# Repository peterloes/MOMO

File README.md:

# Multifunctional mainboard to observe and manipulate organisms (MOMO)
[\[paper\]](https://besjournals.onlinelibrary.wiley.com/doi/full/10.1111/1365-2656.13160) 2.3 Nest and feeder monitoring system

Authors: Loës P., Skripsky P., Kempenaers B. (2019) 

Platform for animal observation and manipulation. 

An efficient system to monitor and control animal behaviour in wildlife
as well as in laboratory settings.

- Targeted manipulation of 1000 and more individuals. Selective feeder.
- Supports a broad range of technical applications like e.g. traps, gates, feeders, lights, cameras
-	Compatible with different RFID systems and triggers
-	Low power consumption and specific data collection lead to long lasting collection periods
-	Applicable world-wide due to its compatibility with different types of radio clock receivers 
-	High observation quality through low disturbance to the animals
- Supports data-transfer to external devices, such as personal computers

- Time Synchronization with atomic clock once a day to ensure optimal data quality
- Application Current Control twice a day
- Forecast for Battery-Change implemented
- Energy Bypass so that Date and Time are maintained even when changing battery
- Hyperterminal Output to get real-time data to the computer/laptop
- Low-Power Device:sleep: 220µA@12V with Light_Barrier awake: 12mA@12V

Bird Feeder Application:

https://github.com/peterloes/MOMO/blob/master/Getting_Started_Tutorial/1_poster_overview_3.pdf

Raw data on SD Card:

https://github.com/peterloes/MOMO/blob/master/Getting_Started_Tutorial/6_rawdata_BOX1005.TXT

Configuration data on SD Card:

https://github.com/peterloes/MOMO/blob/master/Software/CONFIG.TXT

Optional components: 

https://github.com/peterloes/Light_Barrier

https://github.com/peterloes/Servo_Engine

https://github.com/peterloes/Linear_Engine

https://github.com/peterloes/Booter_RFID-MS_MOMO_TAMDL

https://github.com/peterloes/Clock_receiver_RFID-MS_MOMO_TAMDL

Manufacture:

https://github.com/peterloes/MOMO/blob/master/Getting_Started_Tutorial/5_Supplier.txt

EXTENSIONS

Application Scales: Outdoor weighing system for animals include RFID-reader

https://github.com/peterloes/Scales

Application Audio: Record and playback soundfiles triggered by (RFID) pit-tag numbers

https://github.com/peterloes/Audio

C is the Greenest Programming Language

To achieve its power and energy-efficiency features, EFM32 products utilize ultralow active and idle power,
fast wakeup and processing times, and most important, the ability to intelligently interact with peripherals
and sensors autonomously without waking up the CPU and consuming more power.

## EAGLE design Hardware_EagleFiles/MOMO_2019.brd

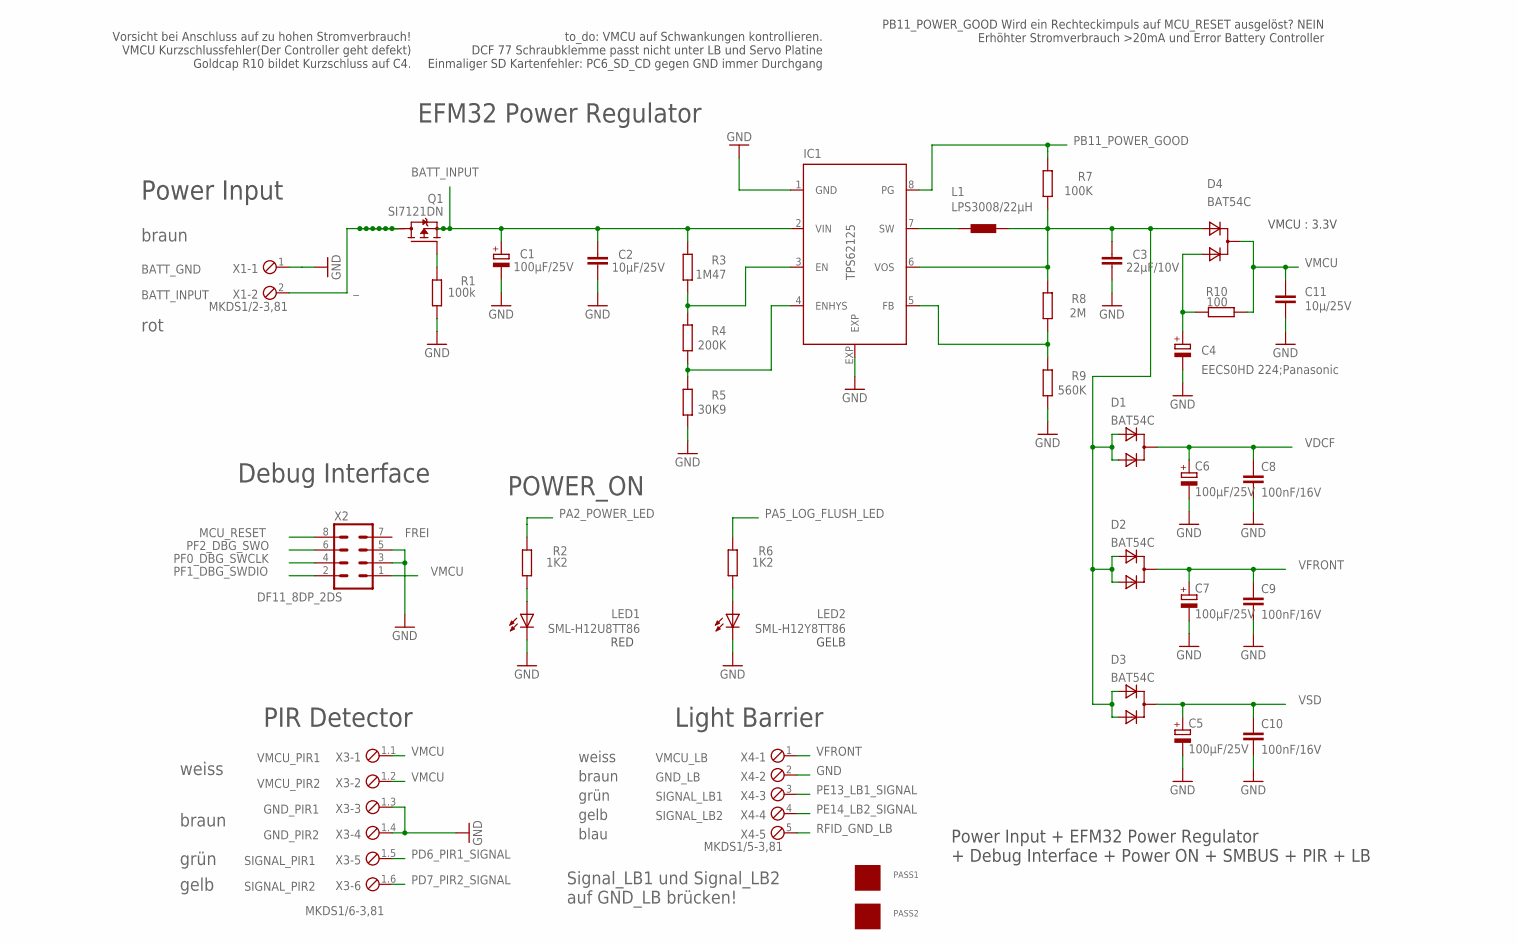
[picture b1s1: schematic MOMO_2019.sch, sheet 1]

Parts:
C1, C5, C6, C7: 100µF/25V; PANASONIC_E
C2: 10µF/25V; C1206
C3: 22µF/10V; C0603
C4: EECS0HD 224;Panasonic; GOLDCAPSPK-V
C8, C9, C10: 100nF/16V; C0805
C11: 10µ/25V; C1206
D1, D2, D3, D4: BAT54C; SOT-23$1
IC1: TPS62125; DSG_PWSO-N8_EXP
L1: LPS3008/22µH; LPS3008
LED1: SML-H12U8TT86; CHIPLED_0805
LED2: SML-H12Y8TT86; CHIPLED_0805
PASS1, PASS2: ROUND_1MM1.5; ROUND2_1.5MM
Q1: SI7121DN; TRANSISTOR-FET_1212-8S
R1: 100k; R0805
R2, R6: 1K2; R0805
R3: 1M47; R0805
R4: 200K; R0805
R5: 30K9; R0805
R7: 100K; R0805
R8: 2M; R0805
R9: 560K; R0805
R10: 100; R0805
X1: MKDS1/2-3,81; 2POL381
X2: DF11_8DP_2DS; DP11_8DP-2DS
X3: MKDS1/6-3,81; 6POL381
X4: MKDS1/5-3,81; 5POL381

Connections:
1: C3.1, D1.2 (A1), D1.3 (A2), D2.2 (A1), D2.3 (A2), D3.2 (A1), D3.3 (A2), D4.2 (A1), IC1.6 (VOS), L1.2, R7.1, R8.2
BATT_INPUT: C1.+, C2.1, IC1.2 (VIN), Q1.1 (S), Q1.2 (S), Q1.3 (S), R3.2; also elsewhere on the board
GND: C1.-, C2.2, C3.2, C4.-, C5.-, C6.-, C7.-, C8.2, C9.2, C10.2, C11.1, IC1.1 (GND), IC1.EXP, LED1.C, LED2.C, R1.1, R5.1, R9.1, X1.1, X2.3, X2.5, X3.1.3, X3.1.4, X4.2; also elsewhere on the board
MCU_RESET: X2.8; also elsewhere on the board
unnamed: LED2.A, R6.2
unnamed: C4.+, D4.3 (A2), R10.2
unnamed: IC1.3 (EN), R3.1, R4.2
unnamed: IC1.4 (ENHYS), R4.1, R5.2
unnamed: IC1.7 (SW), L1.1
unnamed: Q1.4 (G), R1.2
unnamed: LED1.A, R2.2
unnamed: IC1.5 (FB), R8.1, R9.2
PA2_POWER_LED: R2.1; also elsewhere on the board
PA5_LOG_FLUSH_LED: R6.1; also elsewhere on the board
PB11_POWER_GOOD: IC1.8 (PG), R7.2; also elsewhere on the board
PD6_PIR1_SIGNAL: X3.1.5; also elsewhere on the board
PD7_PIR2_SIGNAL: X3.1.6; also elsewhere on the board
PE13_LB1_SIGNAL: X4.3; also elsewhere on the board
PE14_LB2_SIGNAL: X4.4; also elsewhere on the board
PF0_DBG_SWCLK: X2.4; also elsewhere on the board
PF1_DBG_SWDIO: X2.2; also elsewhere on the board
PF2_DBG_SWO: X2.6; also elsewhere on the board
RFID_GND_LB: X4.5; also elsewhere on the board
VDCF: C6.+, C8.1, D1.1 (C); also elsewhere on the board
VFRONT: C7.+, C9.1, D2.1 (C), X4.1
VMCU: C11.2, D4.1 (C), R10.1, X2.1, X3.1.1, X3.1.2; also elsewhere on the board
VSD: C5.+, C10.1, D3.1 (C); also elsewhere on the board
_: Q1.5 (D), Q1.6 (D), Q1.7 (D), Q1.8 (D), Q1.9 (D), Q1.10 (D), Q1.11 (D), X1.2

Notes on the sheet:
BATT_GND
BATT_INPUT
Power Input + EFM32 Power Regulator + Debug Interface + Power ON + SMBUS + PIR + LB
Power Input
EFM32 Power Regulator
Debug Interface
POWER_ON
FREI
SIGNAL_PIR1
VMCU_PIR1
VMCU_PIR2
GND_PIR1
GND_PIR2
SIGNAL_PIR2
VMCU : 3.3V
weiss
braun
grün
gelb
VMCU_LB
GND_LB
SIGNAL_LB1
SIGNAL_LB2
PIR Detector
Light Barrier
RED
GELB
blau
rot
to_do: VMCU auf Schwankungen kontrollieren. DCF 77 Schraubklemme passt nicht unter LB und Servo Platine Einmaliger SD Kartenfehler: PC6_SD_CD gegen GND immer Durchgang
Vorsicht bei Anschluss auf zu hohen Stromverbrauch! VMCU Kurzschlussfehler(Der Controller geht defekt) Goldcap R10 bildet Kurzschluss auf C4.
PB11_POWER_GOOD Wird ein Rechteckimpuls auf MCU_RESET ausgelöst? NEIN Erhöhter Stromverbrauch >20mA und Error Battery Controller
Signal_LB1 und Signal_LB2 auf GND_LB brücken!

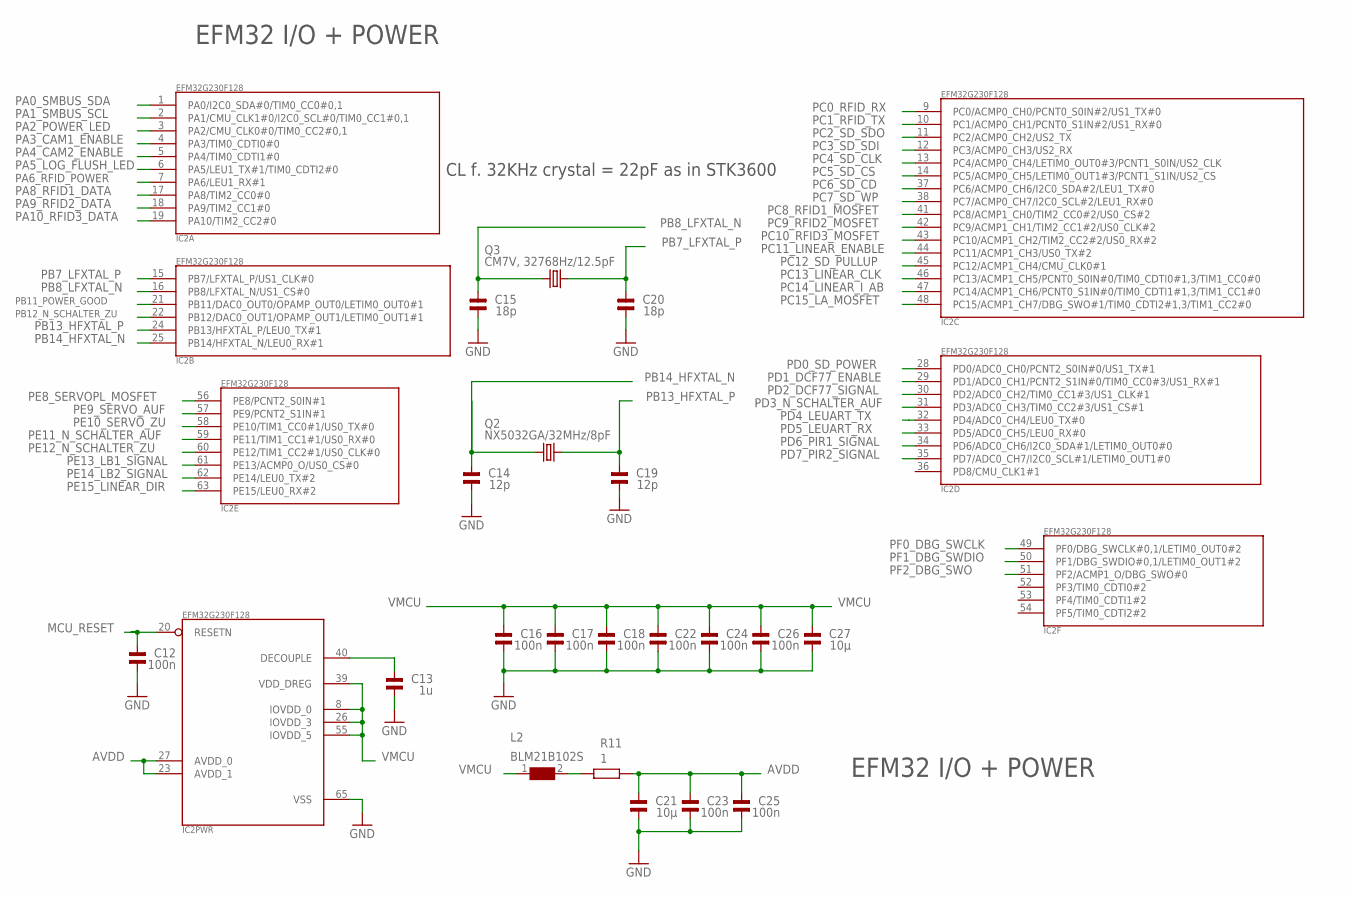
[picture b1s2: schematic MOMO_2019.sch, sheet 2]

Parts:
C12, C16, C17, C18, C22, C23, C24, C25, C26: 100n; 0805
C13: 1u; 0805
C14, C19: 12p; 0805
C15, C20: 18p; 0805
C21, C27: 10µ; 0805
IC2: EFM32G230F128; QFN64
L2: BLM21B102S; 0805
Q2: NX5032GA/32MHz/8pF; CRYSTAL2P5.0X3.2
Q3: CM7V, 32768Hz/12.5pF; CRYSTAL2P3.2X1.5
R11: 1; R0805

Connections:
AVDD: C21.2, C23.2, C25.2, IC2.23 (AVDD_1), IC2.27 (AVDD_0), R11.2
GND: C12.1, C13.1, C14.1, C15.1, C16.1, C17.1, C18.1, C19.1, C20.1, C21.1, C22.1, C23.1, C24.1, C25.1, C26.1, C27.1, IC2.65 (VSS); also elsewhere on the board
MCU_RESET: C12.2, IC2.20 (RESETN); also elsewhere on the board
unnamed: L2.2, R11.1
unnamed: C13.2, IC2.40 (DECOUPLE)
PA0_SMBUS_SDA: IC2.1 (PA0/I2C0_SDA#0/TIM0_CC0#0,1); also elsewhere on the board
PA1_SMBUS_SCL: IC2.2 (PA1/CMU_CLK1#0/I2C0_SCL#0/TIM0_CC1#0,1); also elsewhere on the board
PA2_POWER_LED: IC2.3 (PA2/CMU_CLK0#0/TIM0_CC2#0,1); also elsewhere on the board
PA3_CAM1_ENABLE: IC2.4 (PA3/TIM0_CDTI0#0); also elsewhere on the board
PA4_CAM2_ENABLE: IC2.5 (PA4/TIM0_CDTI1#0); also elsewhere on the board
PA5_LOG_FLUSH_LED: IC2.6 (PA5/LEU1_TX#1/TIM0_CDTI2#0); also elsewhere on the board
PA6_RFID_POWER: IC2.7 (PA6/LEU1_RX#1); also elsewhere on the board
PA8_RFID1_DATA: IC2.17 (PA8/TIM2_CC0#0); also elsewhere on the board
PA9_RFID2_DATA: IC2.18 (PA9/TIM2_CC1#0); also elsewhere on the board
PA10_RFID3_DATA: IC2.19 (PA10/TIM2_CC2#0); also elsewhere on the board
PB7_LFXTAL_P: C20.2, IC2.15 (PB7/LFXTAL_P/US1_CLK#0), Q3.2
PB8_LFXTAL_N: C15.2, IC2.16 (PB8/LFXTAL_N/US1_CS#0), Q3.1
PB11_POWER_GOOD: IC2.21 (PB11/DAC0_OUT0/OPAMP_OUT0/LETIM0_OUT0#1); also elsewhere on the board
PB12_N_SCHALTER_ZU: IC2.22 (PB12/DAC0_OUT1/OPAMP_OUT1/LETIM0_OUT1#1); also elsewhere on the board
PB13_HFXTAL_P: C19.2, IC2.24 (PB13/HFXTAL_P/LEU0_TX#1), Q2.2
PB14_HFXTAL_N: C14.2, IC2.25 (PB14/HFXTAL_N/LEU0_RX#1), Q2.1
PC0_RFID_RX: IC2.9 (PC0/ACMP0_CH0/PCNT0_S0IN#2/US1_TX#0); also elsewhere on the board
PC1_RFID_TX: IC2.10 (PC1/ACMP0_CH1/PCNT0_S1IN#2/US1_RX#0); also elsewhere on the board
PC2_SD_SDO: IC2.11 (PC2/ACMP0_CH2/US2_TX); also elsewhere on the board
PC3_SD_SDI: IC2.12 (PC3/ACMP0_CH3/US2_RX); also elsewhere on the board
PC4_SD_CLK: IC2.13 (PC4/ACMP0_CH4/LETIM0_OUT0#3/PCNT1_S0IN/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); also elsewhere on the board
PC5_SD_CS: IC2.14 (PC5/ACMP0_CH5/LETIM0_OUT1#3/PCNT1_S1IN/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); also elsewhere on the board
PC6_SD_CD: IC2.37 (PC6/ACMP0_CH6/I2C0_SDA#2/LEU1_TX#0); also elsewhere on the board
PC7_SD_WP: IC2.38 (PC7/ACMP0_CH7/I2C0_SCL#2/LEU1_RX#0); also elsewhere on the board
PC8_RFID1_MOSFET: IC2.41 (PC8/ACMP1_CH0/TIM2_CC0#2/US0_CS#2); also elsewhere on the board
PC9_RFID2_MOSFET: IC2.42 (PC9/ACMP1_CH1/TIM2_CC1#2/US0_CLK#2); also elsewhere on the board
PC10_RFID3_MOSFET: IC2.43 (PC10/ACMP1_CH2/TIM2_CC2#2/US0_RX#2); also elsewhere on the board
PC11_LINEAR_ENABLE: IC2.44 (PC11/ACMP1_CH3/US0_TX#2); also elsewhere on the board
PC12_SD_PULLUP: IC2.45 (PC12/ACMP1_CH4/CMU_CLK0#1); also elsewhere on the board
PC13_LINEAR_CLK: IC2.46 (PC13/ACMP1_CH5/PCNT0_S0IN#0/TIM0_CDTI0#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); also elsewhere on the board
PC14_LINEAR_I_AB: IC2.47 (PC14/ACMP1_CH6/PCNT0_S1IN#0/TIM0_CDTI1#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); also elsewhere on the board
PC15_LA_MOSFET: IC2.48 (PC15/ACMP1_CH7/DBG_SWO#1/TIM0_CDTI2#1,3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); also elsewhere on the board
PD0_SD_POWER: IC2.28 (PD0/ADC0_CH0/PCNT2_S0IN#0/US1_TX#1); also elsewhere on the board
PD1_DCF77_ENABLE: IC2.29 (PD1/ADC0_CH1/PCNT2_S1IN#0/TIM0_CC0#3/US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); also elsewhere on the board
PD2_DCF77_SIGNAL: IC2.30 (PD2/ADC0_CH2/TIM0_CC1#3/US1_CLK#1); also elsewhere on the board
PD3_N_SCHALTER_AUF: IC2.31 (PD3/ADC0_CH3/TIM0_CC2#3/US1_CS#1); also elsewhere on the board
PD4_LEUART_TX: IC2.32 (PD4/ADC0_CH4/LEU0_TX#0); also elsewhere on the board
PD5_LEUART_RX: IC2.33 (PD5/ADC0_CH5/LEU0_RX#0); also elsewhere on the board
PD6_PIR1_SIGNAL: IC2.34 (PD6/ADC0_CH6/I2C0_SDA#1/LETIM0_OUT0#0); also elsewhere on the board
PD7_PIR2_SIGNAL: IC2.35 (PD7/ADC0_CH7/I2C0_SCL#1/LETIM0_OUT1#0); also elsewhere on the board
PE8_SERVOPL_MOSFET: IC2.56 (PE8/PCNT2_S0IN#1); also elsewhere on the board
PE9_SERVO_AUF: IC2.57 (PE9/PCNT2_S1IN#1); also elsewhere on the board
PE10_SERVO_ZU: IC2.58 (PE10/TIM1_CC0#1/US0_TX#0); also elsewhere on the board
PE11_N_SCHALTER_AUF: IC2.59 (PE11/TIM1_CC1#1/US0_RX#0); also elsewhere on the board
PE12_N_SCHALTER_ZU: IC2.60 (PE12/TIM1_CC2#1/US0_CLK#0); also elsewhere on the board
PE13_LB1_SIGNAL: IC2.61 (PE13/ACMP0_O/US0_CS#0); also elsewhere on the board
PE14_LB2_SIGNAL: IC2.62 (PE14/LEU0_TX#2); also elsewhere on the board
PE15_LINEAR_DIR: IC2.63 (PE15/LEU0_RX#2); also elsewhere on the board
PF0_DBG_SWCLK: IC2.49 (PF0/DBG_SWCLK#0,1/LETIM0_OUT0#2); also elsewhere on the board
PF1_DBG_SWDIO: IC2.50 (PF1/DBG_SWDIO#0,1/LETIM0_OUT1#2); also elsewhere on the board
PF2_DBG_SWO: IC2.51 (PF2/ACMP1_O/DBG_SWO#0); also elsewhere on the board
VMCU: C16.2, C17.2, C18.2, C22.2, C24.2, C26.2, C27.2, IC2.8 (IOVDD_0), IC2.26 (IOVDD_3), IC2.39 (VDD_DREG), IC2.55 (IOVDD_5), L2.1; also elsewhere on the board

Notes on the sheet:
EFM32 I/O + POWER
CL f. 32KHz crystal = 22pF as in STK3600

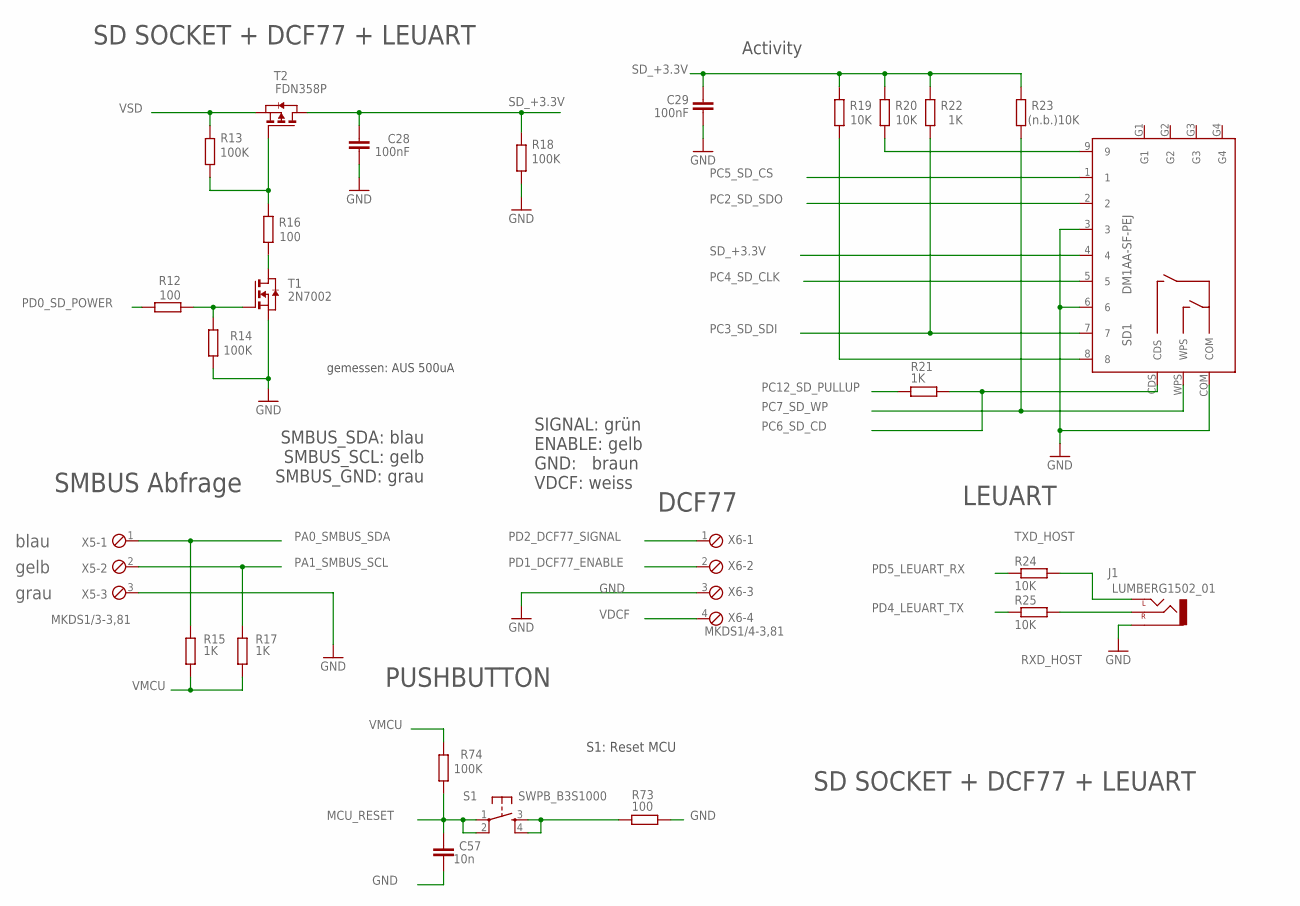
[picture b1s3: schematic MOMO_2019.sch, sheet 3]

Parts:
C28, C29: 100nF; C0603
C57: 10n; C0603
J1: LUMBERG1502_01
R12, R16, R73: 100; R0805
R13, R14, R18, R74: 100K; R0805
R15, R17, R21, R22: 1K; R0805
R19, R20, R24, R25: 10K; R0805
R23: (n.b.)10K; R0805
S1: SWPB_B3S1000; DTSM-6
SD1: DM1AA-SF-PEJ
T1: 2N7002; ZETEX_SOT-23
T2: FDN358P; ZETEX_SOT-23
X5: MKDS1/3-3,81; 3POL381
X6: MKDS1/4-3,81; 4POL381

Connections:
GND: C28.2, C29.2, C57.1, J1.P$1 (1-SLEEVE), R14.1, R18.1, R73.2, SD1.3, SD1.6, SD1.COM, T1.2 (S), X5.3, X6.3; also elsewhere on the board
MCU_RESET: C57.2, R74.1, S1.1, S1.2; also elsewhere on the board
unnamed: R13.1, R16.2, T2.3 (G)
unnamed: R16.1, T1.1 (D)
unnamed: R12.1, R14.2, T1.3 (G)
unnamed: R20.1, SD1.9
unnamed: R19.1, SD1.8
unnamed: R73.1, S1.3, S1.4
PA0_SMBUS_SDA: R15.1, X5.1; also elsewhere on the board
PA1_SMBUS_SCL: R17.1, X5.2; also elsewhere on the board
PC2_SD_SDO: SD1.2; also elsewhere on the board
PC3_SD_SDI: R22.1, SD1.7; also elsewhere on the board
PC4_SD_CLK: SD1.5; also elsewhere on the board
PC5_SD_CS: SD1.1; also elsewhere on the board
PC6_SD_CD: R21.1, SD1.CDS; also elsewhere on the board
PC7_SD_WP: R23.1, SD1.WPS; also elsewhere on the board
PC12_SD_PULLUP: R21.2; also elsewhere on the board
PD0_SD_POWER: R12.2; also elsewhere on the board
PD1_DCF77_ENABLE: X6.2; also elsewhere on the board
PD2_DCF77_SIGNAL: X6.1; also elsewhere on the board
PD4_LEUART_TX: R25.1; also elsewhere on the board
PD5_LEUART_RX: R24.1; also elsewhere on the board
RXD_HOST: J1.P$3 (3-RIGHT), R25.2
SD_+3.3V: C28.1, C29.1, R18.2, R19.2, R20.2, R22.2, R23.2, SD1.4, T2.1 (D)
TXD_HOST: J1.P$2 (2-LEFT), R24.2
VDCF: X6.4; also elsewhere on the board
VMCU: R15.2, R17.2, R74.2; also elsewhere on the board
VSD: R13.2, T2.2 (S); also elsewhere on the board

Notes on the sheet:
LEUART
gemessen: AUS 500uA
DCF77
Activity
SD SOCKET + DCF77 + LEUART
SIGNAL: grün ENABLE: gelb GND: braun VDCF: weiss
SMBUS Abfrage
blau
gelb
grau
SMBUS_SDA: blau SMBUS_SCL: gelb SMBUS_GND: grau
PUSHBUTTON
S1: Reset MCU

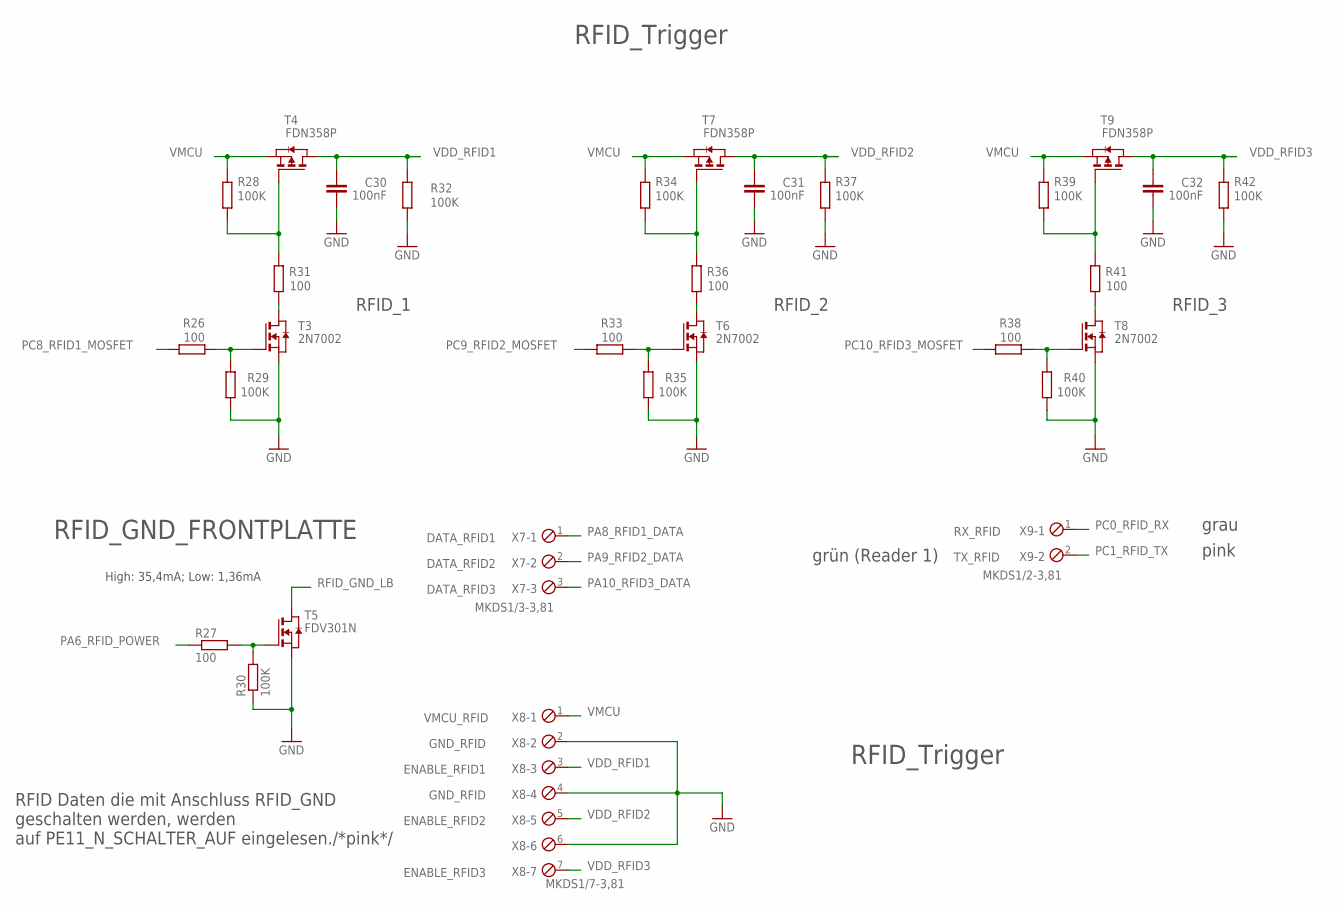
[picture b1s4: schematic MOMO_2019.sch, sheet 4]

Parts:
C30, C31, C32: 100nF; C0603
R26, R27, R31, R33, R36, R38, R41: 100; R0805
R28, R29, R30, R32, R34, R35, R37, R39, R40, R42: 100K; R0805
T3, T6, T8: 2N7002; ZETEX_SOT-23
T4, T7, T9: FDN358P; ZETEX_SOT-23
T5: FDV301N; SOT-23
X7: MKDS1/3-3,81; 3POL381
X8: MKDS1/7-3,81; 7POL381
X9: MKDS1/2-3,81; 2POL381

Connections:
GND: C30.2, C31.2, C32.2, R29.1, R30.1, R32.1, R35.1, R37.1, R40.1, R42.1, T3.2 (S), T5.2 (S), T6.2 (S), T8.2 (S), X8.2, X8.4, X8.6; also elsewhere on the board
unnamed: R28.1, R31.2, T4.3 (G)
unnamed: R31.1, T3.1 (D)
unnamed: R26.1, R29.2, T3.3 (G)
unnamed: R39.1, R41.2, T9.3 (G)
unnamed: R41.1, T8.1 (D)
unnamed: R27.2, R30.2, T5.3 (G)
unnamed: R38.1, R40.2, T8.3 (G)
unnamed: R34.1, R36.2, T7.3 (G)
unnamed: R36.1, T6.1 (D)
unnamed: R33.1, R35.2, T6.3 (G)
PA6_RFID_POWER: R27.1; also elsewhere on the board
PA8_RFID1_DATA: X7.1; also elsewhere on the board
PA9_RFID2_DATA: X7.2; also elsewhere on the board
PA10_RFID3_DATA: X7.3; also elsewhere on the board
PC0_RFID_RX: X9.1; also elsewhere on the board
PC1_RFID_TX: X9.2; also elsewhere on the board
PC8_RFID1_MOSFET: R26.2; also elsewhere on the board
PC9_RFID2_MOSFET: R33.2; also elsewhere on the board
PC10_RFID3_MOSFET: R38.2; also elsewhere on the board
RFID_GND_LB: T5.1 (D); also elsewhere on the board
VDD_RFID1: C30.1, R32.2, T4.1 (D), X8.3
VDD_RFID2: C31.1, R37.2, T7.1 (D), X8.5
VDD_RFID3: C32.1, R42.2, T9.1 (D), X8.7
VMCU: R28.2, R34.2, R39.2, T4.2 (S), T7.2 (S), T9.2 (S), X8.1; also elsewhere on the board

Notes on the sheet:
RFID_Trigger
RFID_1
RFID_3
RFID_2
RFID_Trigger
RX_RFID
TX_RFID
ENABLE_RFID1
ENABLE_RFID2
ENABLE_RFID3
VMCU_RFID
GND_RFID
DATA_RFID1
DATA_RFID2
DATA_RFID3
pink
grau
High: 35,4mA; Low: 1,36mA
RFID_GND_FRONTPLATTE
grün (Reader 1)
RFID Daten die mit Anschluss RFID_GND geschalten werden, werden auf PE11_N_SCHALTER_AUF eingelesen./*pink*/

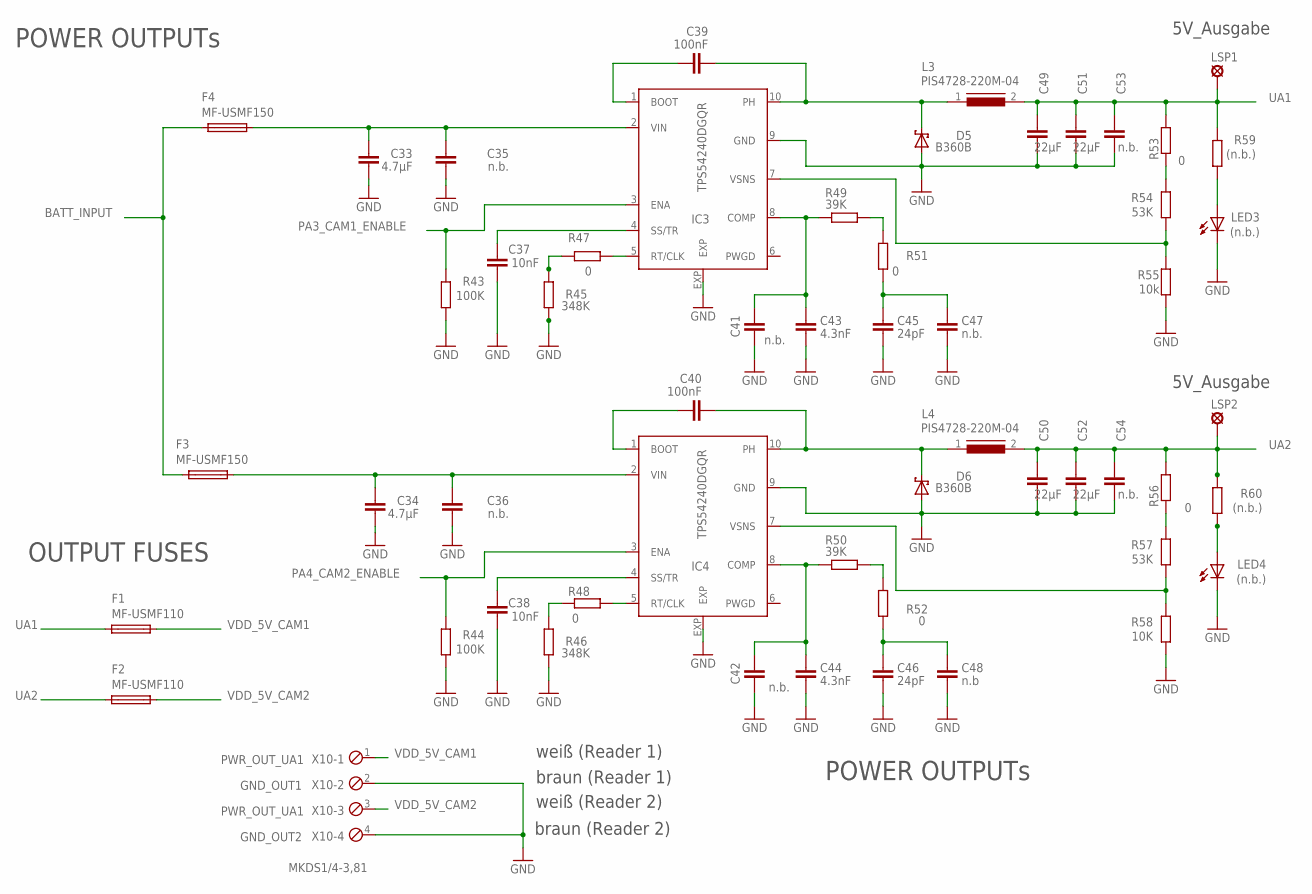
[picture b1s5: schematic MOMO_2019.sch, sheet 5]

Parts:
C33, C34: 4.7µF; C1210
C35, C36, C53, C54: n.b.; C1210
C37, C38: 10nF; C0603
C39, C40: 100nF; C0603
C41, C42, C47: n.b.; C0603
C43, C44: 4.3nF; C0603
C45, C46: 24pF; C0603
C48: n.b; C0603
C49, C50, C51, C52: 22µF; C1210
D5, D6: B360B; SMB
F1, F2: MF-USMF110; PFUF_1210POLY
F3, F4: MF-USMF150; PFUF_1210POLY
IC3, IC4: TPS54240DGQR; S-PDSO-G10
L3, L4: PIS4728-220M-04; DR127
LED3, LED4: (n.b.); CHIPLED_0805
LSP1, LSP2: (n.b.)SE13; SE13
R43, R44: 100K; R0805
R45, R46: 348K; R0805
R47, R48, R51, R52, R53, R56: 0; R0805
R49, R50: 39K; R0805
R54, R57: 53K; R0805
R55: 10k; R0805
R58: 10K; R0805
R59, R60: (n.b.); R0805
X10: MKDS1/4-3,81; 4POL381

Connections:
BATT_INPUT: F3.P$1 (1), F4.P$1 (1); also elsewhere on the board
GND: C33.2, C34.2, C35.2, C36.2, C37.2, C38.2, C41.2, C42.2, C43.2, C44.2, C45.2, C46.2, C47.2, C48.2, C49.2, C50.2, C51.2, C52.2, C53.2, C54.2, D5.A, D6.A, IC3.9 (GND), IC3.EXP, IC4.9 (GND), IC4.EXP, LED3.C, LED4.C, R43.1, R44.1, R45.1, R46.1, R55.1, R58.1, X10.2, X10.4; also elsewhere on the board
unnamed: C39.2, IC3.1 (BOOT)
unnamed: C39.1, D5.C, IC3.10 (PH), L3.1
unnamed: C37.1, IC3.4 (SS/TR)
unnamed: C41.1, C43.1, IC3.8 (COMP), R49.1
unnamed: C45.1, C47.1, R51.1
unnamed: IC3.7 (VSNS), R54.1, R55.2
unnamed: C40.2, IC4.1 (BOOT)
unnamed: C40.1, D6.C, IC4.10 (PH), L4.1
unnamed: C38.1, IC4.4 (SS/TR)
unnamed: C42.1, C44.1, IC4.8 (COMP), R50.1
unnamed: C46.1, C48.1, R52.1
unnamed: IC4.7 (VSNS), R57.1, R58.2
unnamed: LED4.A, R60.1
unnamed: R45.2, R47.1
unnamed: R46.2, R48.1
unnamed: IC3.5 (RT/CLK), R47.2
unnamed: R49.2, R51.2
unnamed: R53.1, R54.2
unnamed: IC4.5 (RT/CLK), R48.2
unnamed: R56.1, R57.2
unnamed: R50.2, R52.2
unnamed: LED3.A, R59.1
unnamed: C33.1, C35.1, F4.P$2 (2), IC3.2 (VIN)
unnamed: C34.1, C36.1, F3.P$2 (2), IC4.2 (VIN)
PA3_CAM1_ENABLE: IC3.3 (ENA), R43.2; also elsewhere on the board
PA4_CAM2_ENABLE: IC4.3 (ENA), R44.2; also elsewhere on the board
UA1: C49.1, C51.1, C53.1, F1.P$1 (1), L3.2, LSP1.MP, R53.2, R59.2
UA2: C50.1, C52.1, C54.1, F2.P$1 (1), L4.2, LSP2.MP, R56.2, R60.2
VDD_5V_CAM1: F1.P$2 (2), X10.1
VDD_5V_CAM2: F2.P$2 (2), X10.3

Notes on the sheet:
5V_Ausgabe
POWER OUTPUTs
OUTPUT FUSES
PWR_OUT_UA1
GND_OUT1
GND_OUT2
weiß (Reader 1)
braun (Reader 1)
weiß (Reader 2)
braun (Reader 2)

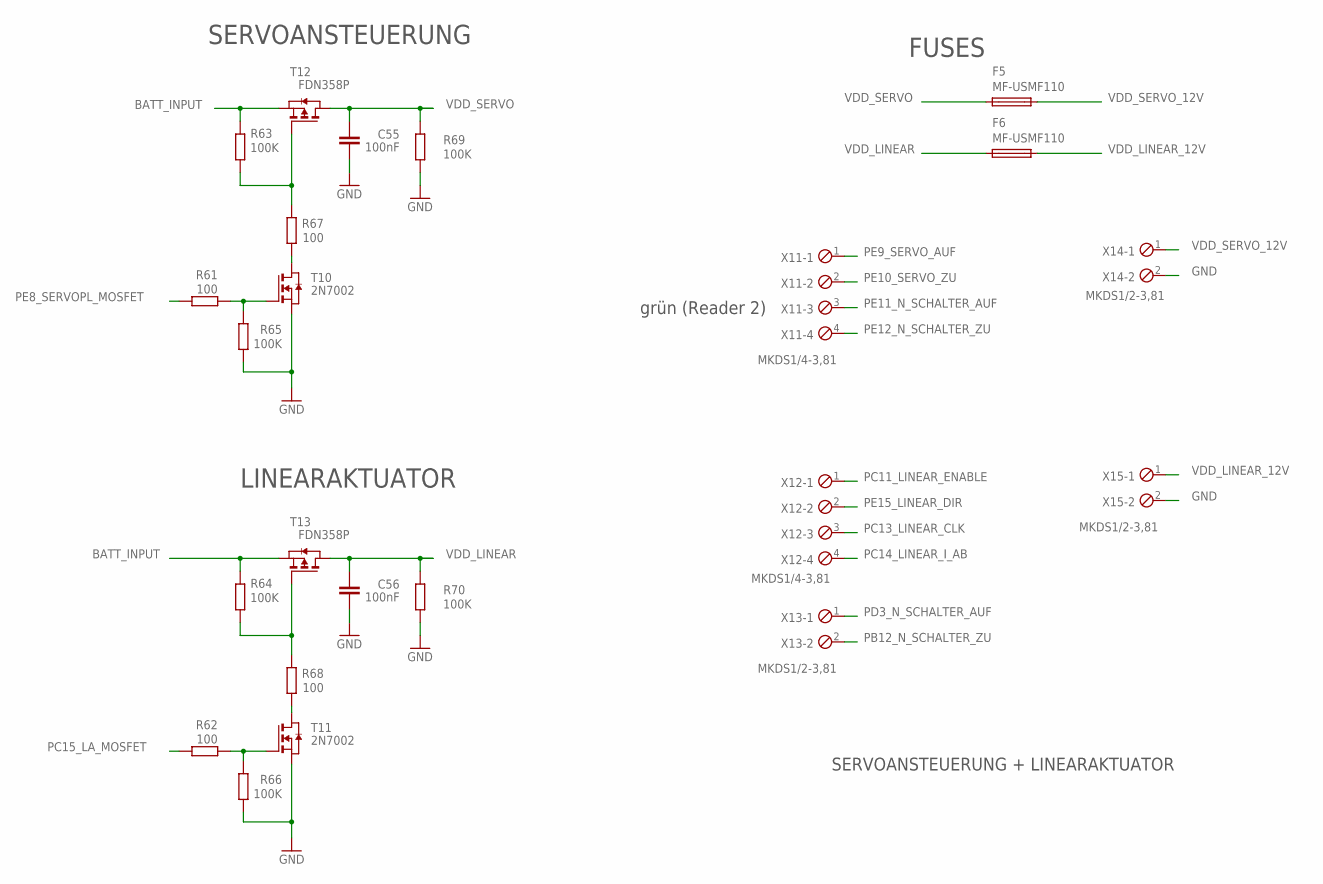
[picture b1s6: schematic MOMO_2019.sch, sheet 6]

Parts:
C55, C56: 100nF; C0603
F5, F6: MF-USMF110; PFUF_1210POLY
R61, R62, R67, R68: 100; R0805
R63, R64, R65, R66, R69, R70: 100K; R0805
T10, T11: 2N7002; ZETEX_SOT-23
T12, T13: FDN358P; ZETEX_SOT-23
X11, X12: MKDS1/4-3,81; 4POL381
X13, X14, X15: MKDS1/2-3,81; 2POL381

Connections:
BATT_INPUT: R63.2, R64.2, T12.2 (S), T13.2 (S); also elsewhere on the board
GND: C55.2, C56.2, R65.1, R66.1, R69.1, R70.1, T10.2 (S), T11.2 (S), X14.2, X15.2; also elsewhere on the board
unnamed: R63.1, R67.2, T12.3 (G)
unnamed: R67.1, T10.1 (D)
unnamed: R61.1, R65.2, T10.3 (G)
unnamed: R64.1, R68.2, T13.3 (G)
unnamed: R68.1, T11.1 (D)
unnamed: R62.1, R66.2, T11.3 (G)
PB12_N_SCHALTER_ZU: X13.2; also elsewhere on the board
PC11_LINEAR_ENABLE: X12.1; also elsewhere on the board
PC13_LINEAR_CLK: X12.3; also elsewhere on the board
PC14_LINEAR_I_AB: X12.4; also elsewhere on the board
PC15_LA_MOSFET: R62.2; also elsewhere on the board
PD3_N_SCHALTER_AUF: X13.1; also elsewhere on the board
PE8_SERVOPL_MOSFET: R61.2; also elsewhere on the board
PE9_SERVO_AUF: X11.1; also elsewhere on the board
PE10_SERVO_ZU: X11.2; also elsewhere on the board
PE11_N_SCHALTER_AUF: X11.3; also elsewhere on the board
PE12_N_SCHALTER_ZU: X11.4; also elsewhere on the board
PE15_LINEAR_DIR: X12.2; also elsewhere on the board
VDD_LINEAR: C56.1, F6.P$1 (1), R70.2, T13.1 (D)
VDD_LINEAR_12V: F6.P$2 (2), X15.1
VDD_SERVO: C55.1, F5.P$1 (1), R69.2, T12.1 (D)
VDD_SERVO_12V: F5.P$2 (2), X14.1

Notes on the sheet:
SERVOANSTEUERUNG
LINEARAKTUATOR
SERVOANSTEUERUNG + LINEARAKTUATOR
FUSES
grün (Reader 2)

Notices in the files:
parts and their libraries:
EnergyMicro: CC0 License
SparkFun-Aesthetics: Licensing: CC v3.0 Share-Alike You are welcome to use this library for commercial purposes.
